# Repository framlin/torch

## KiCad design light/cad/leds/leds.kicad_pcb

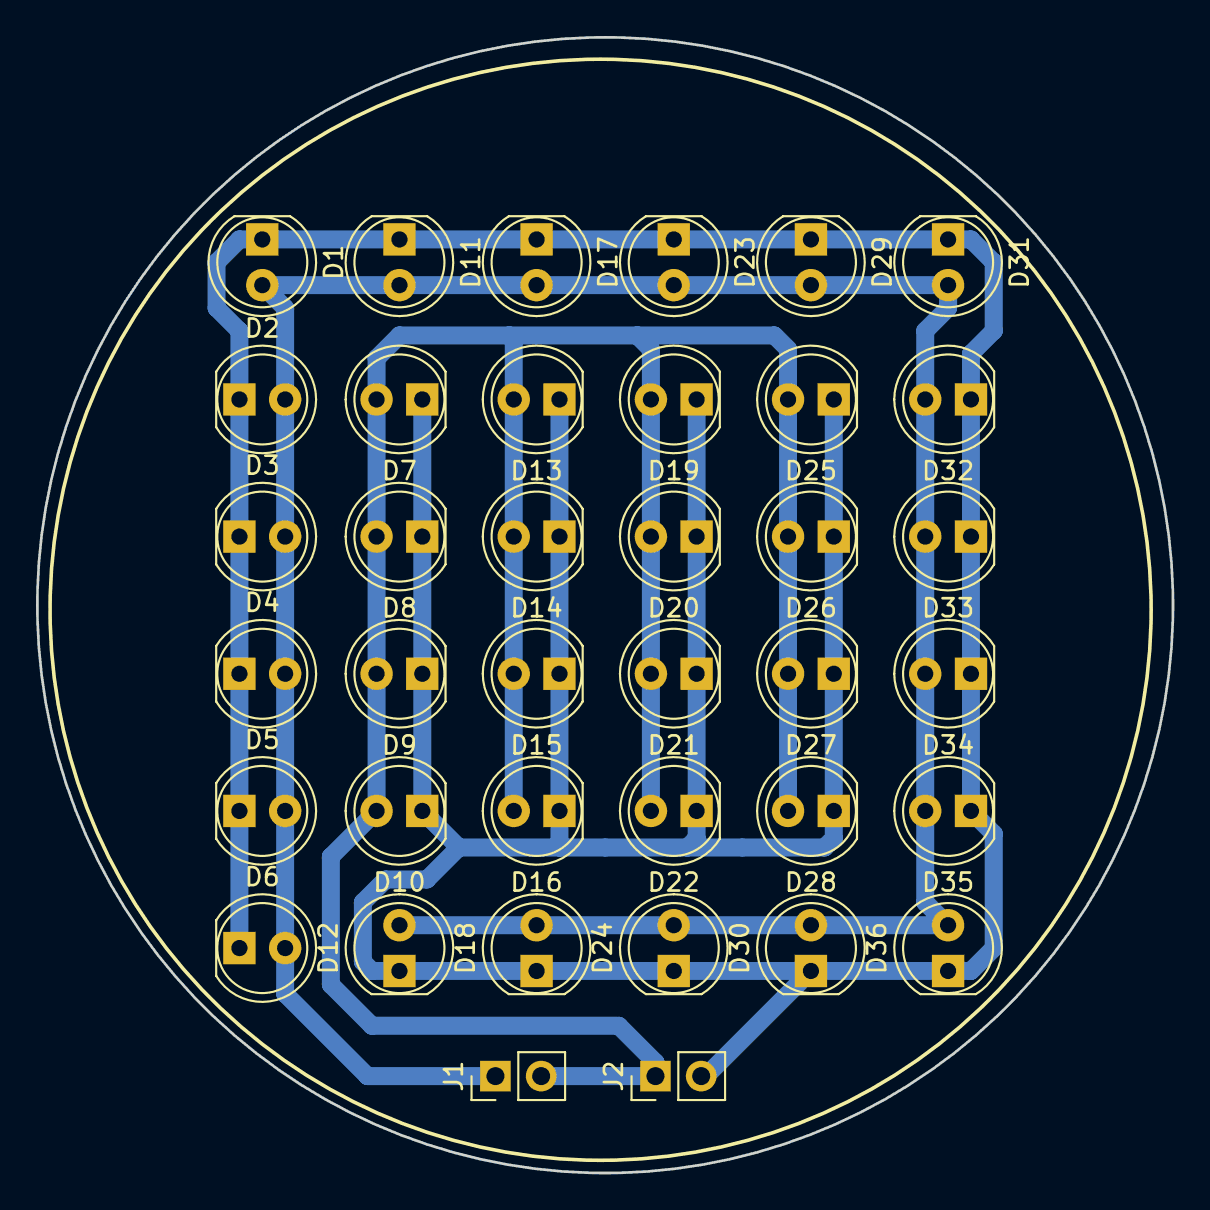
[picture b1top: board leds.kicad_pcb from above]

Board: 2 copper layers, 63.1 x 63.1 mm, 38 parts (0 on the bottom side), 3 nets.

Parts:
D1, D2, D3, D4, D5, D6, D7, D8, D9, D10, D11, D12, D13, D14, D15, D16, D17, D18, D19, D20, D21, D22, D23, D24, D25, D26, D27, D28, D29, D30, D31, D32, D33, D34, D35, D36: LED; LED_D5.0mm
J1, J2: Conn_01x02; Pin_Header_Straight_1x02_Pitch2.54mm

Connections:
GND: D1.1, D2.1, D3.1, D4.1, D5.1, D6.1, D7.1, D8.1, D9.1, D10.1, D11.1, D12.1, D13.1, D14.1, D15.1, D16.1, D17.1, D18.1, D19.1, D20.1, D21.1, D22.1, D23.1, D24.1, D25.1, D26.1, D27.1, D28.1, D29.1, D30.1, D31.1, D32.1, D33.1, D34.1, D35.1, D36.1, J2.2
Spott_Circle: D7.2, D8.2, D9.2, D10.2, D13.2, D14.2, D15.2, D16.2, D19.2, D20.2, D21.2, D22.2, D25.2, D26.2, D27.2, D28.2, J1.2, J2.1
Wide_Circle: D1.2, D2.2, D3.2, D4.2, D5.2, D6.2, D11.2, D12.2, D17.2, D18.2, D23.2, D24.2, D29.2, D30.2, D31.2, D32.2, D33.2, D34.2, D35.2, D36.2, J1.1

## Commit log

2017-12-10 led schema and svg sketh
2017-12-10 first pcb steps
2017-12-10 optimze design, finalize layout
2017-12-10 remove via
2017-12-11 new fs structure
2017-12-12 add body-model and 3d-printing-gcode
2017-12-12 use 15 degree 0.2 tip for GC
